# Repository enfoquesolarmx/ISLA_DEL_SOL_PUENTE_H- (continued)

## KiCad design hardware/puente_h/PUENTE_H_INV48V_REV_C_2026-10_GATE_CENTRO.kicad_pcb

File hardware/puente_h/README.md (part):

# Tarjeta de potencia: Puente H SPWM 48 V

**Isla del Sol — Puente H, prototipo V0.1** · Archivo: `PUENTE_H_INV48V_REV_C_2026-10_GATE_CENTRO` · Estado: **lista para fabricar** · pendiente de validar en banco

> ⚠️ **Seguridad:** esta tarjeta maneja hasta ~35 A en el lado de 48 V, y el transformador entrega **127 V AC, que pueden ser mortales**. Una batería de 48 V entrega cientos de amperes en un corto. Arma y prueba primero con una fuente limitada en corriente y con voltaje reducido (sección 12).

Es la tarjeta principal del inversor/cargador: contiene los cuatro MOSFET del puente H, el banco de capacitores del bus, los shunts para medir corriente y los conectores para los módulos universales (gate drivers, sensor de corriente y buck de 15 V). La lógica de control vive en otra tarjeta.

---

*Prototipo de trinchera en perspectiva (render 3D de KiCad, **rehecho el 2026-11-17 con los pines ya movidos**): los cuatro IRF100P219 en sus disipadores Fischer SK 129, los Rubycon entre las dos filas de MOSFET, los films rojos de entrada, los sockets J10 y J9 para los gate drivers, J3 para el sensor DC y la salida J8 con su resistencia fusible R14.*

---

## 1. Características

| Parámetro | Valor |
| --- | --- |
| Entrada | Batería de 48 V (bus de ~42 a ~60 V) |
| Potencia | 1000 W como inversor; 1 kVA como cargador |
| Salida | Primario del transformador de 60 Hz (rango compatible 24–28 V / 120 V, sección 9) |
| Topología | Puente H completo: dos piernas, un MOSFET alto y uno bajo en cada una |
| MOSFET | 4 × Infineon **IRF100P219** (100 V, 1.4 mΩ típico), TO-247 vertical |
| Disipadores | 4 × Fischer **SK 129 50.8 STS** (5.3 °C/W), soldados a la tarjeta |
| Modulación (inversor) | **Híbrida:** pierna A a 24 kHz, pierna B a 60 Hz |
| Modulación (cargador) | **Unipolar:** las dos piernas a 24 kHz |
| Capacitores de bus | 4 × Rubycon **100ZLH820MEFC18X40** + 4 × 10 µF + 4 × 4.7 µF X7R + film 1 µF |
| Medición de corriente | Shunts Littelfuse SSA2512 de 1 mΩ en el retorno de la batería (1 a 3 piezas) |
| Cobre | **2 capas, 1 oz (35 µm)**: es la condición de diseño, porque es lo que se consigue en trinchera |
| Tamaño de la tarjeta | ~166 × 140 mm |

---

## 2. Archivos

| Archivo | Contenido |
| --- | --- |
| `PUENTE_H_INV48V_REV_C_2026-10_GATE_CENTRO.kicad_pro` | Proyecto de **KiCad 10** (ábrelo para cargar todo). ⚠️ KiCad 9 ya no lo abre: ver la nota de formato abajo |
| `PUENTE_H_INV48V_REV_C_2026-10_GATE_CENTRO.kicad_sch` | Esquemático principal (hoja raíz A3 por bloques A–I, KiCad 10) |
| `CAPACITORES.kicad_sch` | Hoja jerárquica: banco de capacitores del bus (antes `CAPASITORES.kicad_sch`) |
| `DISIPADORES.kicad_sch` | Hoja jerárquica: disipadores (antes `untitled.kicad_sch`) |
| `ESTUDIOS.kicad_sch` | Hoja jerárquica sin conexiones: las tres láminas de estudio (red de compuerta y comparación de MOSFET), sección 6.1 |
| `PUENTE_H_INV48V_REV_C_2026-10_GATE_CENTRO.kicad_pcb` | Layout |
| `Heatsink_Fischer_SK129-STS_50.8mm.step` | Modelo 3D del disipador Fischer SK 129 50.8 STS (hecho con las coordenadas de la huella oficial de KiCad) |
| `Disipador_V8511Y_equiv.step` | Modelo 3D aproximado de un disipador equivalente (versión anterior, ya no se usa en el layout) |
| `SSA2512_Littelfuse_Kelvin.kicad_mod` · `SSA2512_Littelfuse.step` | Huella y modelo 3D del shunt (los mismos que en la carpeta del sensor) |
| `auditoria/` | Auditoría de corriente y temperatura del layout: herramientas, figuras y [README](auditoria/README.md) |

> ⚠️ **Formato: el proyecto está en KiCad 10 y KiCad 9 ya no lo abre.** KiCad no sabe guardar hacia atrás. En Debian estable el paquete es 9.0.2 y en backports 9.0.8, así que para abrirlo hay que instalar el Flatpak oficial:
>
> ```
> flatpak install --from https://flathub.org/repo/appstream/org.kicad.KiCad.flatpakref
> ```

---

## 3. Cómo está organizada

*Hoja raíz (KiCad 9, A3) por bloques, pensada para quien arma y repara:*

| Bloque | Contenido |
| --- | --- |
| **A** | Entrada de batería (Faston J5/J6 = BAT+, J1/J2 = BAT−) |
| **B** | Shunts R16/R28/R17 con sus Kelvin NT5/NT6 y el sensor J3 |
| **C** | Pierna A (VS1, 24 kHz): Q1/Q2 con su red de compuerta, Kelvin y bornes J24/J27 |
| **D** | Pierna B (VS2, 60 Hz): Q3/Q4, igual que la A, con bornes J23/J22 |
| **E** | Sockets J10 (A) y J9 (B) de los gate drivers |
| **F** | Alimentación **15V_GA** (J7, LED D6) y **15V_GB** (J4, LED D5) |
| **G** | Salida J8 al buck, con R14 |
| **H** | Hojas jerárquicas CAPACITORES, DISIPADORES y ESTUDIOS |
| **I** | Notas al día y guía rápida de trinchera |

*Cada bloque lleva su nota: qué hace, qué medir y qué pasa si algo va mal.*

```
 BATERÍA 48 V
   (+)──Faston J5, J6────────────── plano 48 V (F.Cu, mitad inferior) ──┬── Q1 (alto A) ── Q3 (alto B)
   (−)──Faston J1, J2── GND_IN ── shunts R16/R28/R17 ── plano GND ──────┴── Q2 (bajo A) ── Q4 (bajo B)
                                     │ Kelvin (NT5/NT6)
                                     └── J3 → módulo SENSOR_DC_INA_COMPARADOR

   Pierna A (24 kHz): Q1 + Q2 → VS1 → bornes J24 + J27 ─┐
                                                        ├── transformador (dos cables en paralelo por lado)
   Pierna B (60 Hz):  Q3 + Q4 → VS2 → bornes J23 + J22 ─┘

   Fila central: C1 C2 (pierna A) · J10 (gate driver A) · C3 C4 (pierna B) · J9 (gate driver B)
   J8: salida de 48 V protegida (R14) para el buck de 15 V de la tarjeta de control
```

*Cara de componentes **sin los modelos 3D puestos**, para que no estorben: con los disipadores montados no se ve nada de lo que hay debajo. Arriba, las huellas de los MOSFET bajos (Q2, Q4) con sus redes de compuerta; en medio, los cuatro Rubycon, los cerámicos de 4.7 µF y los sockets J10 ("24K") y J9 ("60HZ"); abajo, los MOSFET altos (Q1, Q3). A la izquierda, los Faston de batería (NEG − / POS +), los shunts y los films C10 (MKS) y C9 (MKP). Las dos franjas amarillas de arriba y abajo son las tiras sin máscara del bus.*

*En cada MOSFET se alcanzan a leer sus tres pines, y ahí se ve el acomodo nuevo: en los altos (abajo) dice `GATE · 48V · VS`, con el drenaje escalonado; en los bajos (arriba) dice `GND · 15V · GATE` con el drenaje conmutado apartado de la compuerta.*

*Vista del editor de PCB de KiCad, con las dos capas encendidas. A la izquierda, la entrada de batería (NEG − arriba, POS + abajo), los shunts y los films C9/C10. En el centro, las dos piernas: los MOSFET bajos con sus disipadores arriba, la fila de Rubycon en medio, sobre la frontera GND / 48 V, y los MOSFET altos abajo. J10 (pierna A, "24K") y J9 (pierna B, "60HZ") son los sockets de los gate drivers. Abajo a la izquierda, R14 y la salida J8 al buck.*

| Zona | Qué hay |
| --- | --- |
| Izquierda | Entrada de batería (Faston), shunts, conector del sensor J3, films C9 y C10, salida J8 al buck |
| Centro izquierda | Pierna A: Q2 arriba (bajo), Q1 abajo (alto), con sus disipadores; C1 y C2 en medio |
| Centro | J10, el socket del gate driver de la pierna A |
| Centro derecha | Pierna B: Q4 arriba (bajo), Q3 abajo (alto); C3 y C4 en medio |
| Derecha | J9, el socket del gate driver de la pierna B |

---

## 4. Conectores

| Ref. | Tipo | Señales | Notas |
| --- | --- | --- | --- |
| J5, J6 | Faston 6.35 mm (TE 63823) | **48 V** de batería | Dos en paralelo, ~15 A cada uno a plena carga. Confirmar la corriente por terminal en la hoja de datos de TE. |
| J1, J2 | Faston 6.35 mm | **GND_IN** (negativo de batería) | Antes de los shunts |
| J24, J27 | Borne M3 con vías | **VS1** | Dos cables en paralelo a una terminal del transformador |
| J23, J22 | Borne M3 con vías | **VS2** | Dos cables en paralelo a la otra terminal |
| J10 | Socket 1 × 9, 2.54 mm | Gate driver de la pierna A | Pinout en la tabla siguiente |
| J9 | Socket 1 × 9, 2.54 mm | Gate driver de la pierna B | Mismo pinout |
| J7 | JST EH 2 pines | **15V_GA** + GND | Alimentación del gate driver A (J10) **solamente** (LED D6) |
| J4 | JST EH 2 pines | **15V_GB** + GND | Alimentación del gate driver B (J9) y del sensor J3 (LED D5) |
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
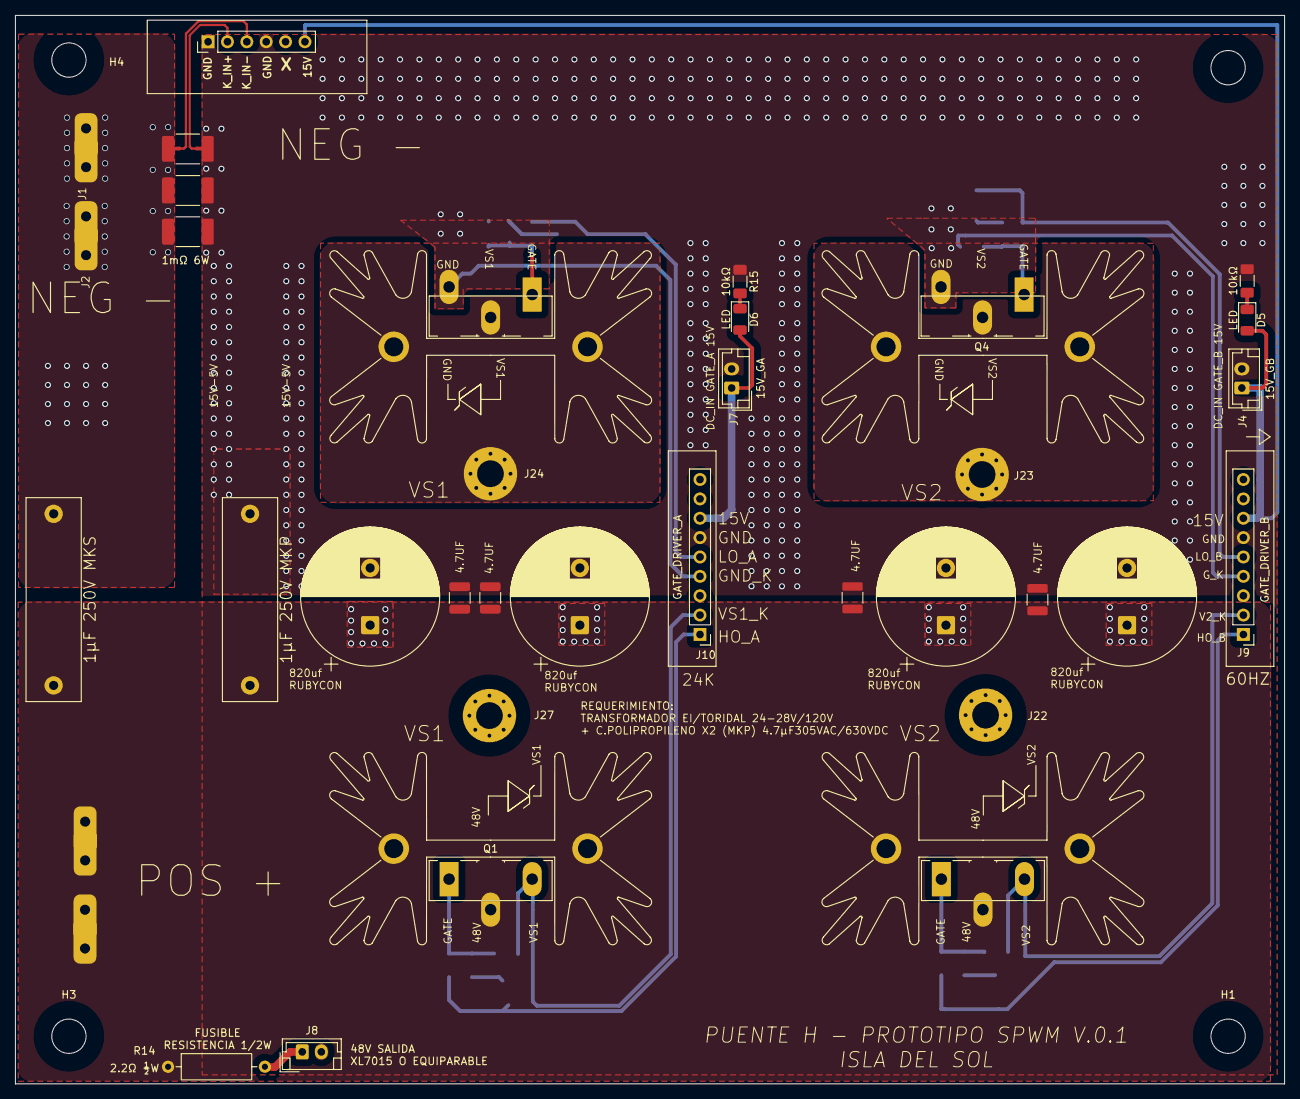
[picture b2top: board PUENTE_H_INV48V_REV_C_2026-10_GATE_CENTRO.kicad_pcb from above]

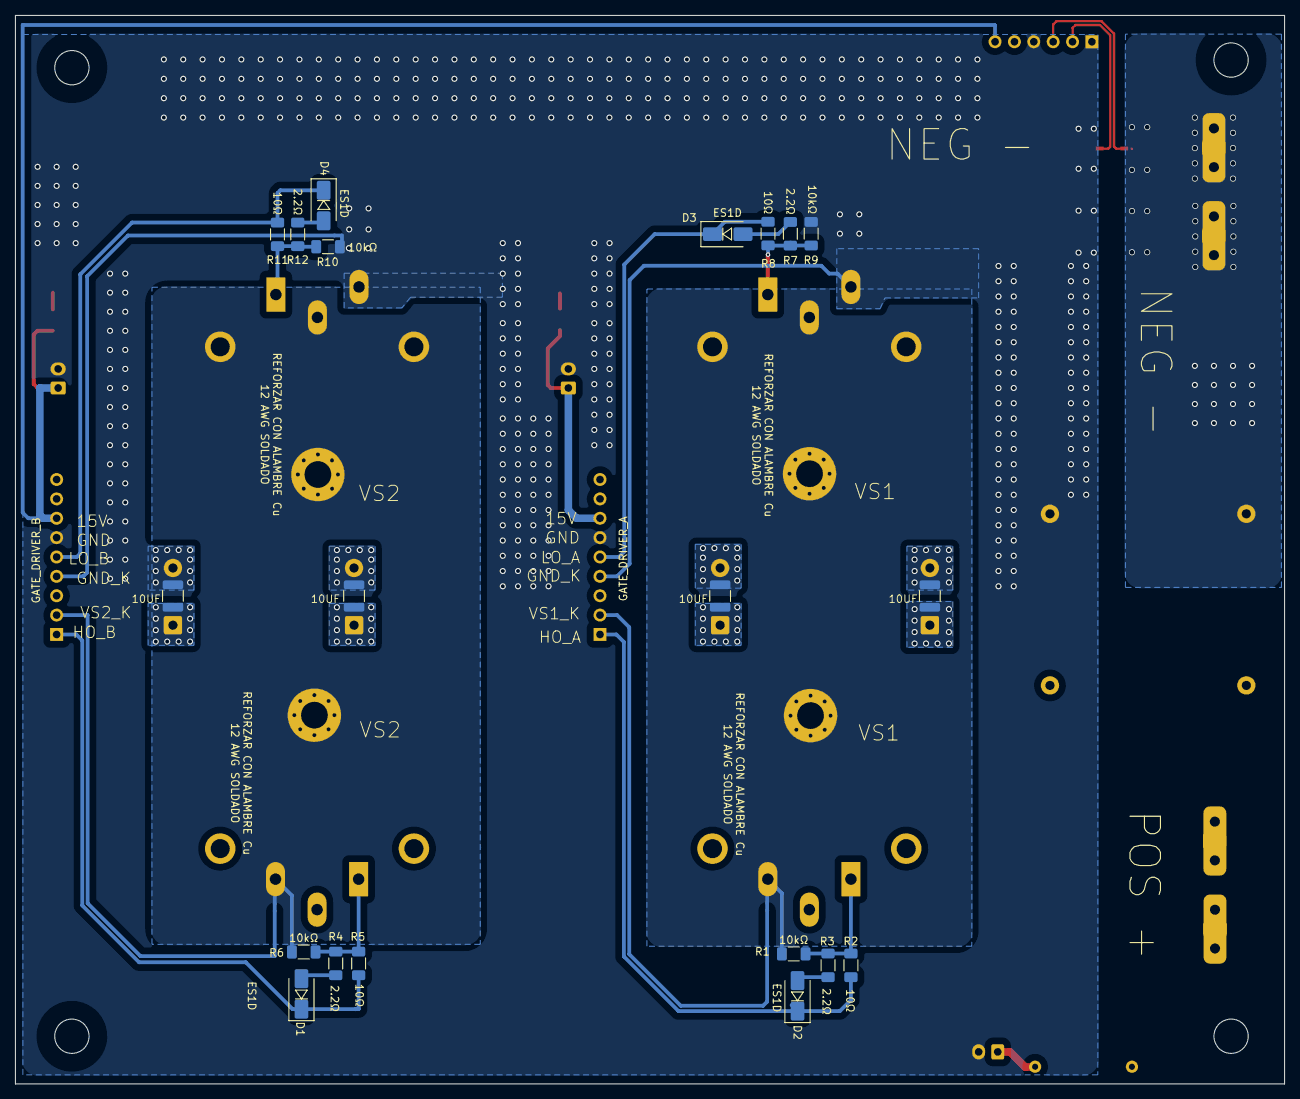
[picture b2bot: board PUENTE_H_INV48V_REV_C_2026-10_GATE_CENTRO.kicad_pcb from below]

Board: 2 copper layers, 166.4 x 140.1 mm, 70 parts (24 on the bottom side), 28 nets.

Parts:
C1, C2, C3, C4: 820µF 100V Rubycon ZLH; CP_Radial_D18.0mm_P7.50mm
C5, C6, C7, C8: 10µF 100V X7R; C_1210_3225Metric
C9: 1µF 250V MKP; C_Rect_L26.5mm_W7.0mm_P22.50mm_MKS4
C10: 1µF 250V MKS; C_Rect_L26.5mm_W7.0mm_P22.50mm_MKS4
C11, C12, C13, C14: 4.7µF 100V X7R; C_1210_3225Metric
D1, D2, D3, D4: ES1D; D_SMA
D5, D6: LED; LED_1206_3216Metric
H1, H2, H3, H4: MountingHole; MountingHole_4.5mm
HS5: DISIPADOR_1; Heatsink_Fischer_SK129-STS_42x25mm_2xDrill2.5mm
HS6: DISIPADOR_3; Heatsink_Fischer_SK129-STS_42x25mm_2xDrill2.5mm
HS7: DISIPADOR_2; Heatsink_Fischer_SK129-STS_42x25mm_2xDrill2.5mm
HS8: DISIPADOR_4; Heatsink_Fischer_SK129-STS_42x25mm_2xDrill2.5mm
J1, J2: BAT− (GND_IN); Faston 63823
J3: SENSOR_DC (llave en 5); PinHeader_1x06_P2.54mm_Vertical
J4: 15V_GB; JST_EH_B2B-EH-A_1x02_P2.50mm_Vertical
J5, J6: BAT+ (48V); Faston 63823
J7: 15V_GA; JST_EH_B2B-EH-A_1x02_P2.50mm_Vertical
J8: 48V → BUCK (≥80 V); JST_EH_B2B-EH-A_1x02_P2.50mm_Vertical
J9: GATE_DRIVER_B; PinHeader_1x09_P2.54mm_Vertical
J10: GATE_DRIVER_A; PinHeader_1x09_P2.54mm_Vertical
J22, J23: VS2; MountingHole_3.5mm_Pad_Via
J24, J27: VS1; MountingHole_3.5mm_Pad_Via
NT1, NT2, NT3, NT4, NT5, NT6: Kelvin; NetTie-2_SMD_Pad0.5mm
Q1, Q2, Q3, Q4: IRF100P219; TO-247-3_Vertical
R1, R6, R9, R10, R13, R15: 10kΩ; R_1206_3216Metric_Pad1.30x1.75mm_HandSolder
R2, R5, R8, R11: 10Ω; R_1206_3216Metric_Pad1.30x1.75mm_HandSolder
R3, R4, R7, R12: 2.2Ω; R_1206_3216Metric_Pad1.30x1.75mm_HandSolder
R14: 2.2Ω ½W; R_Axial_DIN0309_L9.0mm_D3.2mm_P12.70mm_Horizontal
R16: 1mΩ 6W (Kelvin, siempre); SSA2512_Littelfuse_Kelvin
R17: 1mΩ 6W (opcional); SSA2512_Littelfuse_Kelvin
R28: 1mΩ 6W; SSA2512_Littelfuse_Kelvin

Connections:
15V_GA: D6.2 (A), J7.1, J10.7
15V_GB: D5.2 (A), J3.6, J4.1, J9.7
48V: C1.1, C2.1, C3.1, C4.1, C5.1, C6.1, C7.1, C8.1, C9.1, C10.1, C11.1, C12.1, C13.1, C14.1, HS5.1, HS7.1, J5.1 (Pin_1_1), J6.1 (Pin_1_1), Q1.2 (D), Q3.2 (D), R14.1
GND: C1.2, C2.2, C3.2, C4.2, C5.2, C6.2, C7.2, C8.2, C9.2, C11.2, C12.2, C13.2, C14.2, J3.1, J3.4, J4.2, J7.2, J8.2, J9.6, J10.6, NT1.2, NT2.2, NT5.2, Q2.3 (S), Q4.3 (S), R9.2, R10.2, R13.1, R15.1, R16.2, R17.2, R28.2
GND_IN: C10.2, J1.1 (Pin_1_1), J2.1 (Pin_1_1), NT6.2, R16.1, R17.1, R28.1
GND_KELVIN_A: J10.4, NT2.1
GND_KELVIN_B: J9.4, NT1.1
HO_A: D2.1 (K), J10.1, R2.1
HO_B: D1.1 (K), J9.1, R5.1
IN+ (Kelvin): J3.2, NT5.1
IN- (Kelvin): J3.3, NT6.1
LO_A: D3.1 (K), J10.5, R8.1
LO_B: D4.1 (K), J9.5, R11.1
unnamed: D1.2 (A), R4.1
unnamed: D2.2 (A), R3.1
unnamed: D3.2 (A), R7.1
unnamed: D4.2 (A), R12.1
unnamed: D5.1 (K), R13.2
unnamed: D6.1 (K), R15.2
unnamed: J8.1, R14.2
unnamed: Q1.1 (G), R1.1, R2.2, R3.2
unnamed: Q2.1 (G), R7.2, R8.2, R9.1
unnamed: Q3.1 (G), R4.2, R5.2, R6.1
unnamed: Q4.1 (G), R10.1, R11.2, R12.2
VS1: HS6.1, J24.1 (Pin_1_1), J27.1 (Pin_1_1), NT4.2, Q1.3 (S), Q2.2 (D), R1.2
VS1_k: J10.2, NT4.1
VS2: HS8.1, J22.1 (Pin_1_1), J23.1 (Pin_1_1), NT3.2, Q3.3 (S), Q4.2 (D), R6.2
VS2_k: J9.2, NT3.1

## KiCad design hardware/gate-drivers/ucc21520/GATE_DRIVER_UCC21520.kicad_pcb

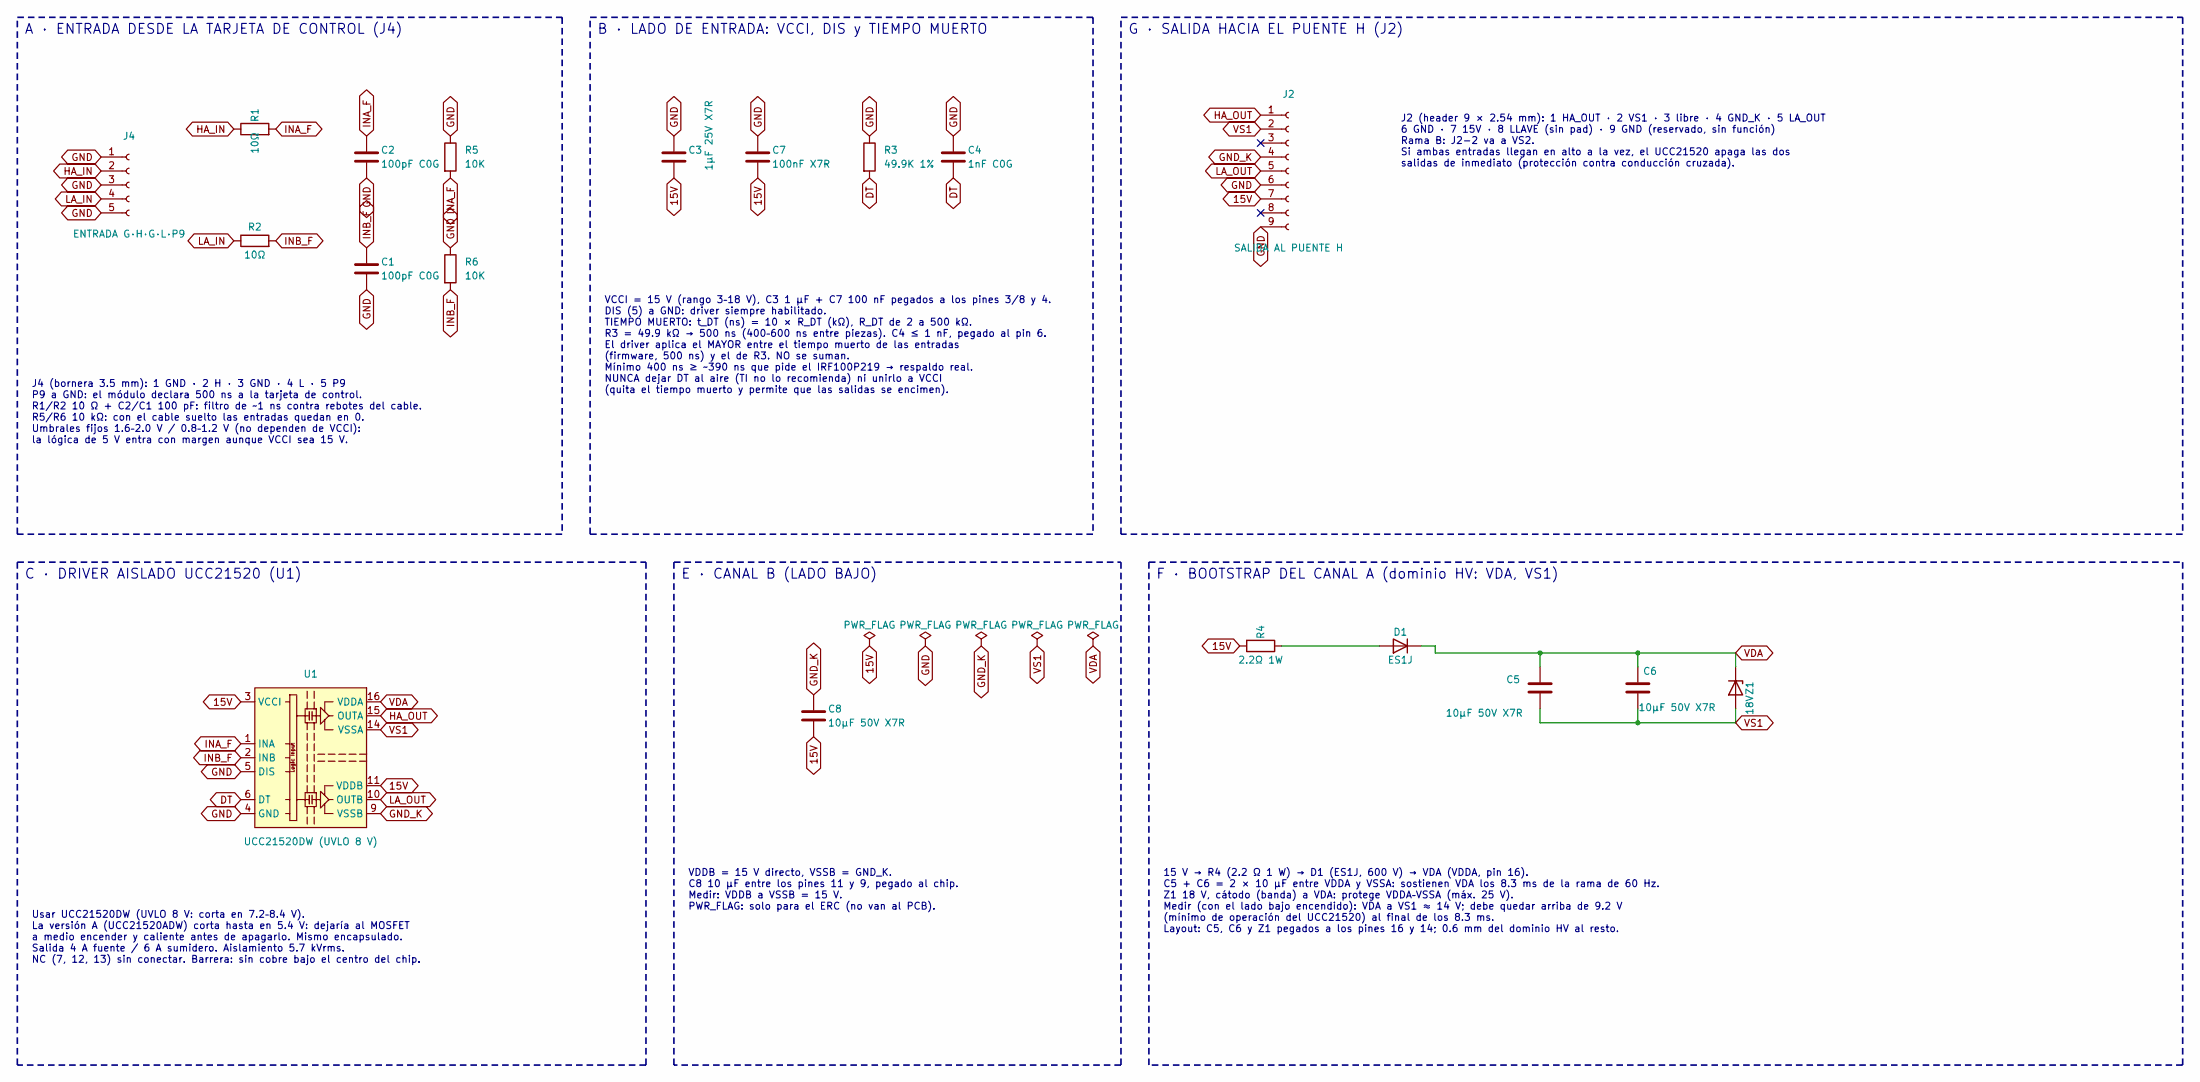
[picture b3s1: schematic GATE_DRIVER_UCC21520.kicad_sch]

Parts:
C1, C2: 100pF C0G; C_1206_3216Metric
C3: 1µF 25V X7R; C_1206_3216Metric
C4: 1nF C0G; C_1206_3216Metric
C5, C6, C8: 10µF 50V X7R; C_1206_3216Metric
C7: 100nF X7R; C_1206_3216Metric
D1: ES1J; D_SMA
J2: SALIDA AL PUENTE H; PinHeader_1x09_P2.54mm_Vertical
J4: ENTRADA G·H·G·L·P9; PhoenixContact_SPT_1.5_5-H-3.5_1x05_P3.5mm_Horizontal
R1, R2: 10Ω; R_1206_3216Metric
R3: 49.9K 1%; R_1206_3216Metric
R4: 2.2Ω 1W; R_1210_3225Metric_Pad1.30x2.65mm_HandSolder
R5, R6: 10K; R_1206_3216Metric
U1: UCC21520DW (UVLO 8 V); SOIC-16W_7.5x10.3mm_P1.27mm
Z1: 18V; D_SMA

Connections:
15V: C3.2, C7.2, C8.2, J2.7, R4.2, U1.3 (VCCI), U1.8 (VCCI), U1.11 (VDDB)
DT: C4.2, R3.2, U1.6 (DT)
GND: C1.2, C2.2, C3.1, C4.1, C7.1, J2.6, J2.9, J4.1, J4.3, J4.5, R3.1, R5.1, R6.1, U1.4 (GND), U1.5 (DIS)
GND_K: C8.1, J2.4, U1.9 (VSSB)
HA_IN: J4.2, R1.1
HA_OUT: J2.1, U1.15 (OUTA)
INA_F: C2.1, R1.2, R5.2, U1.1 (INA)
INB_F: C1.1, R2.2, R6.2, U1.2 (INB)
LA_IN: J4.4, R2.1
LA_OUT: J2.5, U1.10 (OUTB)
unnamed: D1.2 (A), R4.1
VDA: C5.2, C6.2, D1.1 (K), U1.16 (VDDA), Z1.1 (K)
VS1: C5.1, C6.1, J2.2, U1.14 (VSSA), Z1.2 (A)

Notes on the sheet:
VCCI = 15 V (rango 3–18 V), C3 1 µF + C7 100 nF pegados a los pines 3/8 y 4. DIS (5) a GND: driver siempre habilitado. TIEMPO MUERTO: t_DT (ns) = 10 × R_DT (kΩ), R_DT de 2 a 500 kΩ. R3 = 49.9 kΩ → 500 ns (400–600 ns entre piezas). C4 ≤ 1 nF, pegado al pin 6. El driver aplica el MAYOR entre el tiemp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
15 V → R4 (2.2 Ω 1 W) → D1 (ES1J, 600 V) → VDA (VDDA, pin 16). C5 + C6 = 2 × 10 µF entre VDDA y VSSA: sostienen VDA los 8.3 ms de la rama de 60 Hz. Z1 18 V, cátodo (banda) a VDA: protege VDDA–VSSA (máx. 25 V). Medir (con el lado bajo encendido): VDA a VS1 ≈ 14 V; debe quedar arriba de 9.2 V (mínimo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
B · LADO DE ENTRADA: VCCI, DIS y TIEMPO MUERTO
A · ENTRADA DESDE LA TARJETA DE CONTROL (J4)
J2 (header 9 × 2.54 mm): 1 HA_OUT · 2 VS1 · 3 libre · 4 GND_K · 5 LA_OUT 6 GND · 7 15V · 8 LLAVE (sin pad) · 9 GND (reservado, sin función) Rama B: J2-2 va a VS2. Si ambas entradas llegan en alto a la vez, el UCC21520 apaga las dos salidas de inmediato (protección contra conducción cruzada).
F · BOOTSTRAP DEL CANAL A (dominio HV: VDA, VS1)
E · CANAL B (LADO BAJO)
VDDB = 15 V directo, VSSB = GND_K. C8 10 µF entre los pines 11 y 9, pegado al chip. Medir: VDDB a VSSB = 15 V. PWR_FLAG: solo para el ERC (no van al PCB).
C · DRIVER AISLADO UCC21520 (U1)
J4 (bornera 3.5 mm): 1 GND · 2 H · 3 GND · 4 L · 5 P9 P9 a GND: el módulo declara 500 ns a la tarjeta de control. R1/R2 10 Ω + C2/C1 100 pF: filtro de ~1 ns contra rebotes del cable. R5/R6 10 kΩ: con el cable suelto las entradas quedan en 0. Umbrales fijos 1.6–2.0 V / 0.8–1.2 V (no dependen de VCCI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
Usar UCC21520DW (UVLO 8 V: corta en 7.2–8.4 V). La versión A (UCC21520ADW) corta hasta en 5.4 V: dejaría al MOSFET a medio encender y caliente antes de apagarlo. Mismo encapsulado. Salida 4 A fuente / 6 A sumidero. Aislamiento 5.7 kVrms. NC (7, 12, 13) sin conectar. Barrera: sin cobre bajo el centr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
G · SALIDA HACIA EL PUENTE H (J2)

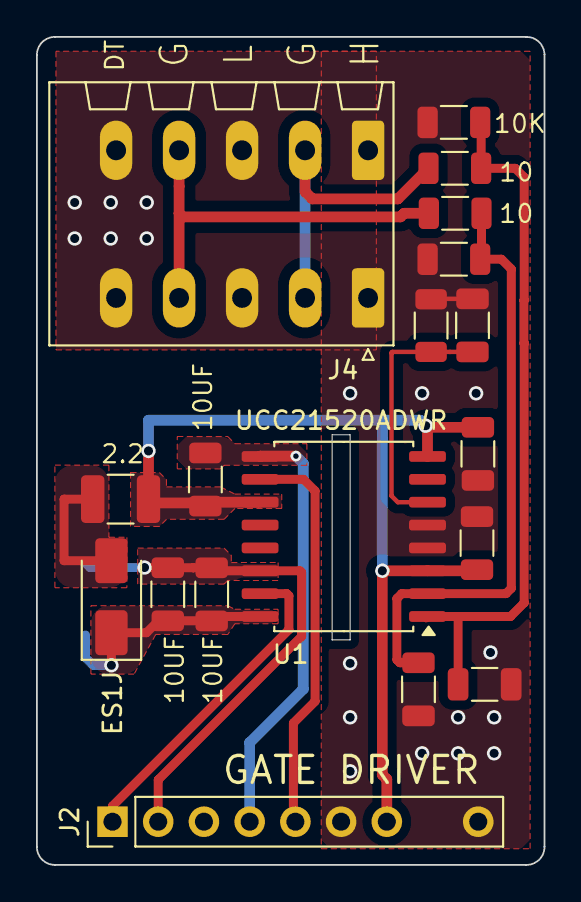
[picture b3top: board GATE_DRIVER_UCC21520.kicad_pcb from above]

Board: 2 copper layers, 28.2 x 46.0 mm, 19 parts (1 on the bottom side), 13 nets.

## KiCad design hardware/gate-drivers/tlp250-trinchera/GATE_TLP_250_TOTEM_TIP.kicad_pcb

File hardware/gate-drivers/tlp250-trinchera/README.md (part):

# Módulo gate driver de medio puente H con TLP250H — modo trinchera (legacy) con tótem TIP41C/TIP42C

**Proyecto:** Puente H — prototipo SPWM "Isla del Sol" (inversor 48 V → 127 V / 60 Hz, 1000 W; modo cargador 1 kVA)
**Módulo:** gate driver de **medio puente H** (una rama: MOSFET alto + MOSFET bajo), de servicio / legacy, intercambiable con IRS2186 y UCC21520DW (misma interfaz, mismo firmware)
**Versión de placa:** V.0.1.NOV.26.J.G
**Estado:** diseño terminado (esquemático y layout); esquemático por bloques con guía de trinchera (2026-11-12). Pendiente: DRC final, fabricación y validación en banco
**Fecha:** 2026-11-02 · **Revisión:** 2026-11-03 (diseño final) · 2026-11-12 (esquemático por bloques)
**Documentos relacionados:** `identificacion_dt_pin9.md` (P9, llave en posición 8, poka-yoke), `compensacion_adaptativa_tiempo_muerto.md`

| Cara de componentes | Cara de soldadura |
| --- | --- |
|  |  |

*Izquierda: arriba, la bornera J1 de entrada, con R3/R4 (330 Ω) en serie con los LED y R1/R2 (10 kΩ) a GND; en medio, los **dos TLP250H** (DIP-8), uno por canal; abajo, los dos tótems **acostados**, TIP41C (NPN) y TIP42C (PNP) con sus resistencias de 2.2 Ω, la red de bootstrap (2.2 Ω 1 W + diodo rápido), los 2 × 10 µF del bootstrap y el header J5. Derecha: las leyendas **"TRENZAR H Y L CON GND"**, **"OPERACIÓN DT TLP250 = 1 µs"** y **"OJO: USAR SILICÓN RTV NEUTRO ENTRE TIPs"**, los 0.1 µF pegados a cada TLP, el 10 µF de 15 V, el zener Z1 de 18 V (1SMA5931B) y la **X** de la llave en la posición 8 de J5.*

*Esquemático por bloques (KiCad 9, hoja A3), pensado para quien arma y repara: **A** entrada J1 · **B** optoacoplador del canal alto (U1) · **C** optoacoplador del canal bajo (U2) · **D** 15 V del canal bajo · **E** bootstrap · **F** tótem alto · **G** tótem bajo · **H** salida J5 · **I** guía rápida de trinchera. Cada bloque dice qué medir y qué pasa si una pieza va al revés.*

## 0. Guía rápida de trinchera

**TLP250 o TLP250H: no son iguales.**

| | TLP250H (diseño) | TLP250 "viejo" (sin H, rescatado) |
| --- | --- | --- |
| Corriente de alimentación | **3 mA máx.** | **11 mA máx.** (7 mA típ.) |
| UVLO | Sí, 7.5–9.5 V | **No especificado** |
| Rama A (24 kHz, el bootstrap se recarga cada 42 µs) | ✓ | ✓ |
| Rama B (60 Hz, 8.3 ms sin recargar) | ✓ VB1 ≈ 11.8 V | ✗ VB1 cae ~5–8 V → el MOSFET alto queda a medio encender y sin protección |

**Regla:** un TLP250 sin "H" solo va en el módulo de la **rama A** (o en las dos en modo cargador, a 24 kHz). En la rama B del inversor, TLP250H u otro módulo (IRS2186, IR2110, UCC21520).

**Antes de soldar:**

| Pieza | Cuidado | Si se hace mal |
| --- | --- | --- |
| U1, U2 | Zócalo DIP-8, muesca hacia el pin 1; revisar la letra **H** | Al revés no enciende; sin H, ver la tabla anterior |
| R3, R4 | **330 Ω** con MCU de 5 V | Con 1 kΩ el LED no enciende bien (~1.7 mA) |
| J5 | **Quitar el pin 8** del header (llave) | El módulo podría entrar al revés |
| Z1 | Banda (cátodo) hacia **VB1** | Pone en corto el bootstrap: el MOSFET alto nunca enciende |
| Q1–Q4 | NPN (TIP41C / D44H11G) en Q1 y Q4, PNP (TIP42C / D45H11G) en Q2 y Q3; acostados, aletas sin tocarse | Cruzados: la salida no sigue a la entrada; aletas juntas: corto VB1–GND_K |
| TIPs | Silicón RTV **neutro** | El acético corroe; el caliente se ablanda a 60–80 °C |

**Prueba sin MOSFET** (15 V en J5-7; J5-4 a la tierra de la fuente; **J5-2 (VS1) unido a J5-4** para que cargue el bootstrap; J1 a la tarjeta de control o a 5 V):

| Medir | Entre | Debe dar |
| --- | --- | --- |
| Salidas con J1 suelto | HA_OUT (J5-1) y LA_OUT (J5-5) | 0 V |
| L = 5 V | LA_OUT a GND_K | ≈ 14 V |
| H = 5 V (después de un pulso de L) | HA_OUT a VS1 | ≈ 13 V |
| Corriente del LED | Caída en R3 o R4 | ≈ 3.3 V (~10 mA) |
| Aislamiento | J1-GND contra GND_K y contra VS1 | **Sin continuidad** |
| Tiempo muerto | Lo que reporta el MCU | **1 µs** (P9 abierto) |

---

## 1. Propósito

### 1.1 Qué maneja este módulo

Cada módulo es un **gate driver de medio puente**: maneja **una rama** del puente H, es decir, el **MOSFET del lado alto** (canal H, referido a VS1, alimentado por bootstrap) y el **MOSFET del lado bajo** (canal L, referido a GND_K) de esa rama.

```
            +48 V
              │
     HA ──► [MOSFET alto]          [MOSFET alto] ◄── HB
              │                         │
              ├── VS1 ──► transformador ◄── VS2 ──┤
              │                         │
     LA ──► [MOSFET bajo]          [MOSFET bajo] ◄── LB
              │                         │
             GND ───────────────────── GND
         └── módulo rama A ──┘    └── módulo rama B ──┘
```

- **El puente H completo usa dos módulos:** uno en la **rama A** (VS1) y otro en la **rama B** (VS2). Son el mismo módulo; en la rama B, las señales "H" y "L" de J1 manejan HB y LB, y el pin "VS1" de J5 se conecta a VS2.
- **Inversor (modulación híbrida):** el módulo de la rama A conmuta a **24 kHz** y el de la rama B a **60 Hz**.
- **Cargador (unipolar):** los dos módulos conmutan a **24 kHz**.
- Cada posición (alto o bajo) puede tener **1 o 2 MOSFET en paralelo** (sección 5).
- Se pueden mezclar tecnologías entre ramas (por ejemplo, UCC21520 en la rama A y TLP250 en la rama B): el MCU lee P9 de cada módulo y, si cualquiera pide 1 µs, usa 1 µs en todo el puente.

### 1.2 Por qué existe

Este módulo existe para **cuando TI o Infineon no llegan**. Es una opción **educativa y de supervivencia**: demuestra que el puente H puede operar con componentes legacy que se consiguen en cualquier tienda de electrónica o se rescatan de equipos viejos (variadores, UPS, soldadoras inverter, fuentes, amplificadores).

| Criterio | Módulos IRS2186 / UCC21520 | Módulo TLP250 (este) |
| --- | --- | --- |
| Costo y número de componentes | **Menor** ✓ | Mayor |
| Desempeño (DT, THD) | **500 ns, THD ~0.8 %** ✓ | 1 µs, THD ~1.6 % |
| Disponibilidad en zonas aisladas | Baja (distribuidor, importación) | **Alta: tienda local o rescate** ✓ |
| Reparación a mano | SMD fino | **DIP y TO-220, cautín común** ✓ |
| Aislamiento entrada / potencia | IRS: no aislado · UCC: aislado | **Aislado (optoacoplador)** ✓ |
| Valor educativo | Driver integrado ("caja negra") | **Cada etapa visible y medible** ✓ |

**Conclusión de diseño:** para producción se usan IRS2186 o UCC21520. Este módulo no busca eficientar; busca que **siempre exista una alternativa**. La infraestructura que lo soporta (P9 y llave en posición 8) cuesta ~1 USD y queda en todas las tarjetas.

---

## 2. Interfaz

### 2.1 J1 — entrada, hacia la tarjeta de control (bornera de 5 terminales)

| Terminal | Señal | En este módulo |
| --- | --- | --- |
| 1 | H | Ánodo del LED de U1 (vía R3) |
| 2 | GND | Cátodo del LED de U1 (trenzar con H) |
| 3 | L | Ánodo del LED de U2 (vía R4) |
| 4 | GND | Cátodo del LED de U2 (trenzar con L) |
| **5** | **P9 — ID DT** | **Abierto, sin pista** → el MCU usa **1 µs** |

- Serigrafía: **"TRENZAR H Y L CON GND"** y **"OPERACION DT TLP250=1US"**.
- **P9 tiene como vecino un GND (terminal 4).** Cable con **puntas estañadas o terminal**, sin hilos sueltos. Opcional: no instalar el cable P9 (la pull-up de la tarjeta de control lee 1 → 1 µs).
- El GND de J1 es el GND del MCU y **no se une a GND_K ni a la potencia dentro del módulo**: el optoacoplador aísla la entrada.

### 2.2 J5 — salida, hacia la tarjeta del puente H (header de 9 posiciones, 2.54 mm)

| Pin | Señal | En este módulo |
| --- | --- | --- |
| 1 | HA_OUT | Emisores del tótem H |
| 2 | VS1 | Referencia del canal H |
| 3 | — | Libre (separación del nodo conmutado) |
| 4 | GND_K | Referencia Kelvin del canal L |
| 5 | LA_OUT | Emisores del tótem L |
| 6 | — | **Sin conectar** en este módulo (la entrada está aislada); marcado como no conectado en el esquemático |
| 7 | 15 V | Alimentación |
| 8 | — | **Llave mecánica:** sin pad; **quitar el pin 8 del header**; "X" en serigrafía |
| 9 | — | Reservado, abierto |

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
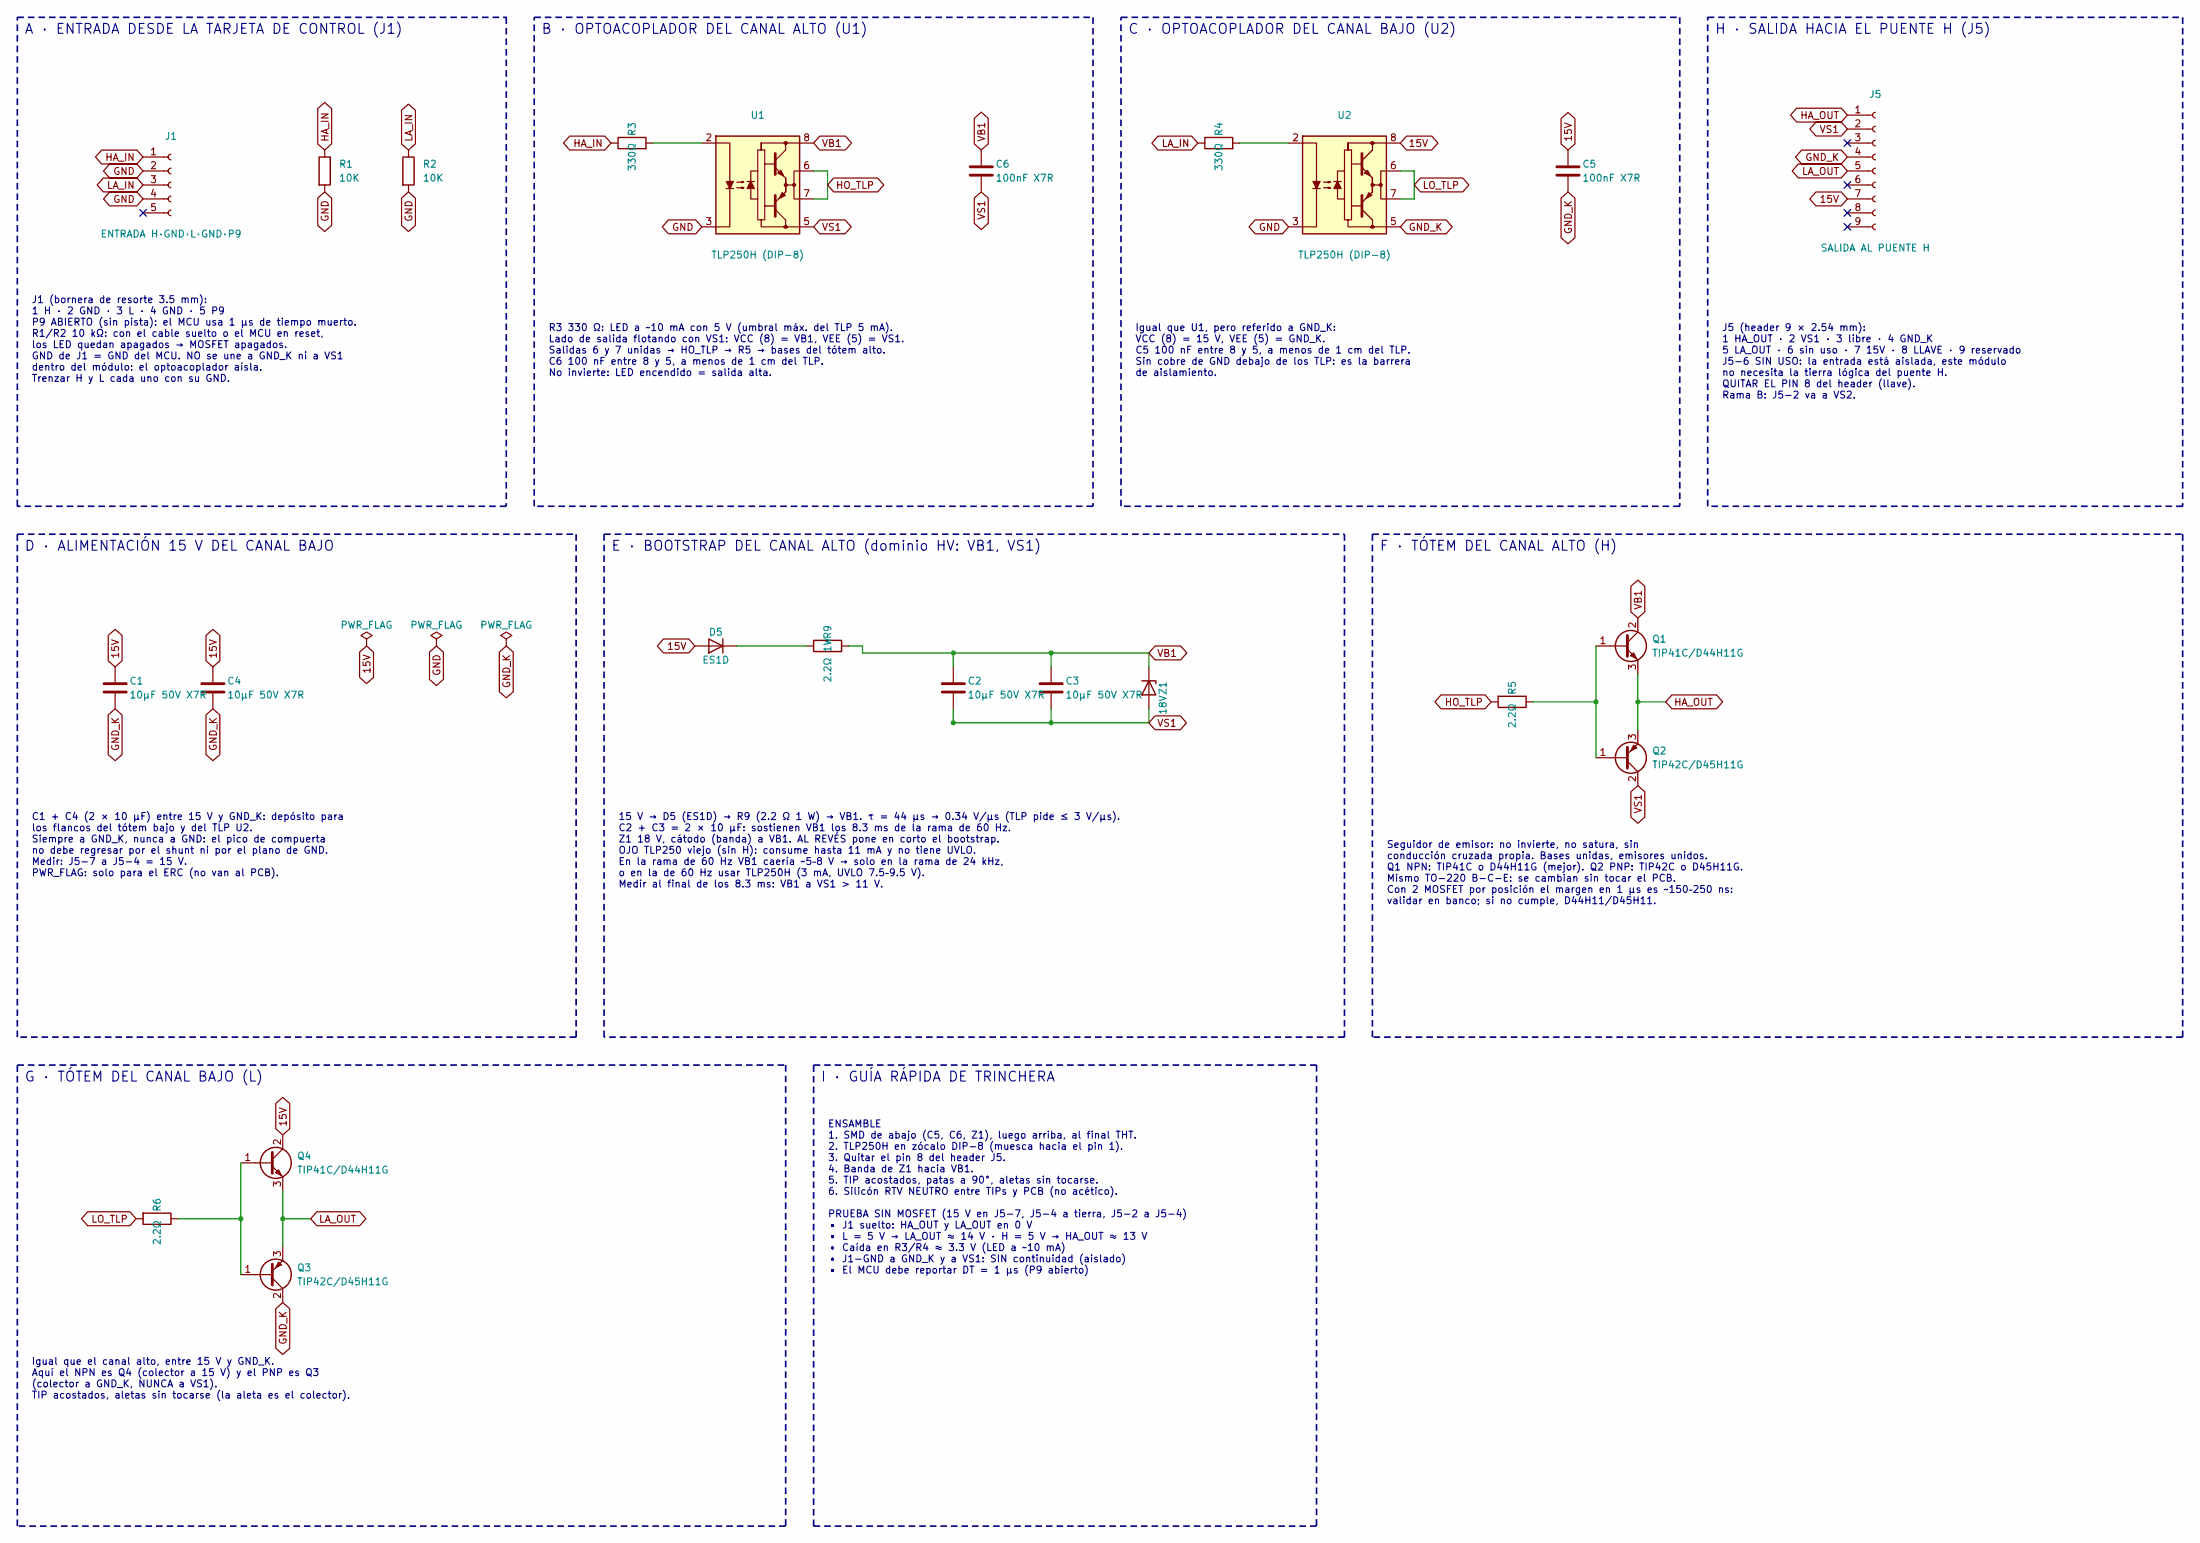
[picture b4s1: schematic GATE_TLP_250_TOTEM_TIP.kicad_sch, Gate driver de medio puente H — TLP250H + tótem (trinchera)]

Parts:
C1, C2, C3, C4: 10µF 50V X7R; C_1206_3216Metric
C5, C6: 100nF X7R; C_1206_3216Metric
D5: ES1D; D_SMA
J1: ENTRADA H·GND·L·GND·P9; PhoenixContact_SPT_1.5_5-H-3.5_1x05_P3.5mm_Horizontal
J5: SALIDA AL PUENTE H; PinHeader_1x09_P2.54mm_Vertical
Q1, Q4: TIP41C/D44H11G; TO-220-3_Vertical
Q2, Q3: TIP42C/D45H11G; TO-220-3_Vertical
R1, R2: 10K; R_1206_3216Metric_Pad1.30x1.75mm_HandSolder
R3, R4: 330Ω; R_1206_3216Metric_Pad1.30x1.75mm_HandSolder
R5, R6: 2.2Ω; R_1206_3216Metric_Pad1.30x1.75mm_HandSolder
R9: 2.2Ω 1W; R_1210_3225Metric
U1, U2: TLP250H (DIP-8); DIP-8_W7.62mm
Z1: 18V; D_SMA

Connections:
15V: C1.1, C4.1, C5.1, D5.2 (A), J5.7, Q4.2 (C), U2.8 (VCC)
GND: J1.2, J1.4, R1.2, R2.2, U1.3 (C), U2.3 (C)
GND_K: C1.2, C4.2, C5.2, J5.4, Q3.2 (C), U2.5 (VEE)
HA_IN: J1.1, R1.1, R3.1
HA_OUT: J5.1, Q1.3 (E), Q2.3 (E)
HO_TLP: R5.2, U1.6 (VO), U1.7 (VO)
LA_IN: J1.3, R2.1, R4.1
LA_OUT: J5.5, Q3.3 (E), Q4.3 (E)
LO_TLP: R6.2, U2.6 (VO), U2.7 (VO)
unnamed: D5.1 (K), R9.2
unnamed: Q1.1 (B), Q2.1 (B), R5.1
unnamed: Q3.1 (B), Q4.1 (B), R6.1
unnamed: R3.2, U1.2 (A)
unnamed: R4.2, U2.2 (A)
VB1: C2.1, C3.1, C6.1, Q1.2 (C), R9.1, U1.8 (VCC), Z1.1 (K)
VS1: C2.2, C3.2, C6.2, J5.2, Q2.2 (C), U1.5 (VEE), Z1.2 (A)

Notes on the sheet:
A · ENTRADA DESDE LA TARJETA DE CONTROL (J1)
J1 (bornera de resorte 3.5 mm): 1 H · 2 GND · 3 L · 4 GND · 5 P9 P9 ABIERTO (sin pista): el MCU usa 1 µs de tiempo muerto. R1/R2 10 kΩ: con el cable suelto o el MCU en reset, los LED quedan apagados → MOSFET apagados. GND de J1 = GND del MCU. NO se une a GND_K ni a VS1 dentro del módulo: el optoaco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
B · OPTOACOPLADOR DEL CANAL ALTO (U1)
R3 330 Ω: LED a ~10 mA con 5 V (umbral máx. del TLP 5 mA). Lado de salida flotando con VS1: VCC (8) = VB1, VEE (5) = VS1. Salidas 6 y 7 unidas → HO_TLP → R5 → bases del tótem alto. C6 100 nF entre 8 y 5, a menos de 1 cm del TLP. No invierte: LED encendido = salida alta.
C · OPTOACOPLADOR DEL CANAL BAJO (U2)
Igual que U1, pero referido a GND_K: VCC (8) = 15 V, VEE (5) = GND_K. C5 100 nF entre 8 y 5, a menos de 1 cm del TLP. Sin cobre de GND debajo de los TLP: es la barrera de aislamiento.
H · SALIDA HACIA EL PUENTE H (J5)
J5 (header 9 × 2.54 mm): 1 HA_OUT · 2 VS1 · 3 libre · 4 GND_K 5 LA_OUT · 6 sin uso · 7 15V · 8 LLAVE · 9 reservado J5-6 SIN USO: la entrada está aislada, este módulo no necesita la tierra lógica del puente H. QUITAR EL PIN 8 del header (llave). Rama B: J5-2 va a VS2.
D · ALIMENTACIÓN 15 V DEL CANAL BAJO
C1 + C4 (2 × 10 µF) entre 15 V y GND_K: depósito para los flancos del tótem bajo y del TLP U2. Siempre a GND_K, nunca a GND: el pico de compuerta no debe regresar por el shunt ni por el plano de GND. Medir: J5-7 a J5-4 = 15 V. PWR_FLAG: solo para el ERC (no van al PCB).
E · BOOTSTRAP DEL CANAL ALTO (dominio HV: VB1, VS1)
15 V → D5 (ES1D) → R9 (2.2 Ω 1 W) → VB1. τ = 44 µs → 0.34 V/µs (TLP pide ≤ 3 V/µs). C2 + C3 = 2 × 10 µF: sostienen VB1 los 8.3 ms de la rama de 60 Hz. Z1 18 V, cátodo (banda) a VB1. AL REVÉS pone en corto el bootstrap. OJO TLP250 viejo (sin H): consume hasta 11 mA y no tiene UVLO. En la rama de 60 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
F · TÓTEM DEL CANAL ALTO (H)
Seguidor de emisor: no invierte, no satura, sin conducción cruzada propia. Bases unidas, emisores unidos. Q1 NPN: TIP41C o D44H11G (mejor). Q2 PNP: TIP42C o D45H11G. Mismo TO-220 B-C-E: se cambian sin tocar el PCB. Con 2 MOSFET por posición el margen en 1 µs es ~150–250 ns: validar en banco; si no 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
G · TÓTEM DEL CANAL BAJO (L)
Igual que el canal alto, entre 15 V y GND_K. Aquí el NPN es Q4 (colector a 15 V) y el PNP es Q3 (colector a GND_K, NUNCA a VS1). TIP acostados, aletas sin tocarse (la aleta es el colector).
I · GUÍA RÁPIDA DE TRINCHERA
ENSAMBLE 1. SMD de abajo (C5, C6, Z1), luego arriba, al final THT. 2. TLP250H en zócalo DIP-8 (muesca hacia el pin 1). 3. Quitar el pin 8 del header J5. 4. Banda de Z1 hacia VB1. 5. TIP acostados, patas a 90°, aletas sin tocarse. 6. Silicón RTV NEUTRO entre TIPs y PCB (no acético). PRUEBA SIN MOSFE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

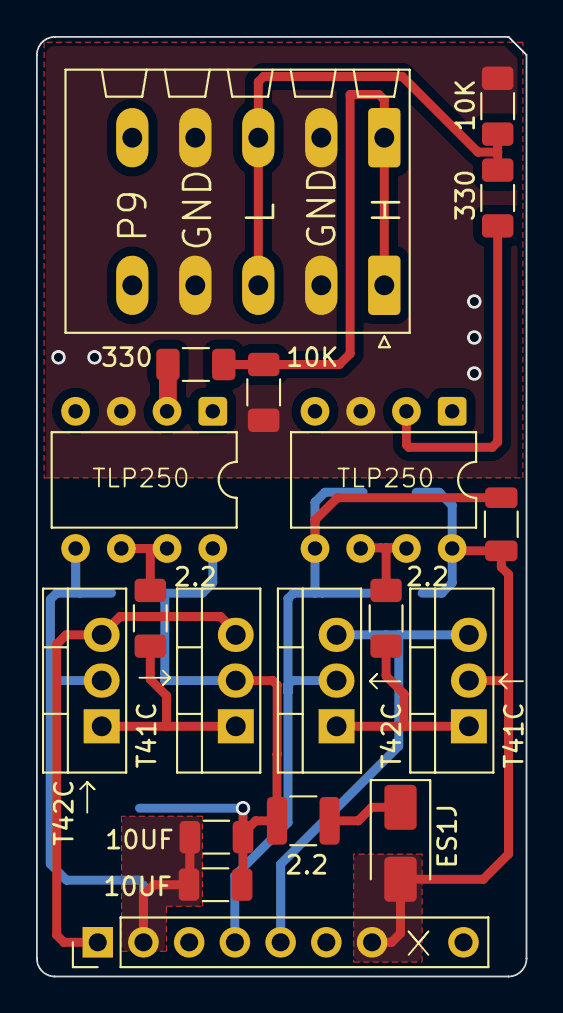
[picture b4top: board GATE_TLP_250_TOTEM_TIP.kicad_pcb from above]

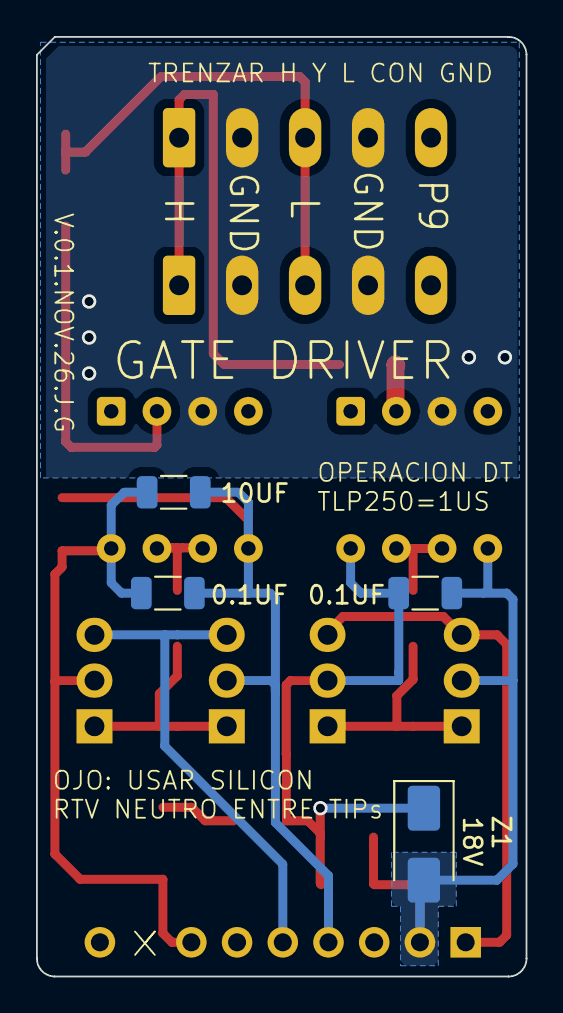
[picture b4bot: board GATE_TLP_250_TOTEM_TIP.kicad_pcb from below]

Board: 2 copper layers, 27.2 x 52.2 mm, 23 parts (4 on the bottom side), 16 nets.
